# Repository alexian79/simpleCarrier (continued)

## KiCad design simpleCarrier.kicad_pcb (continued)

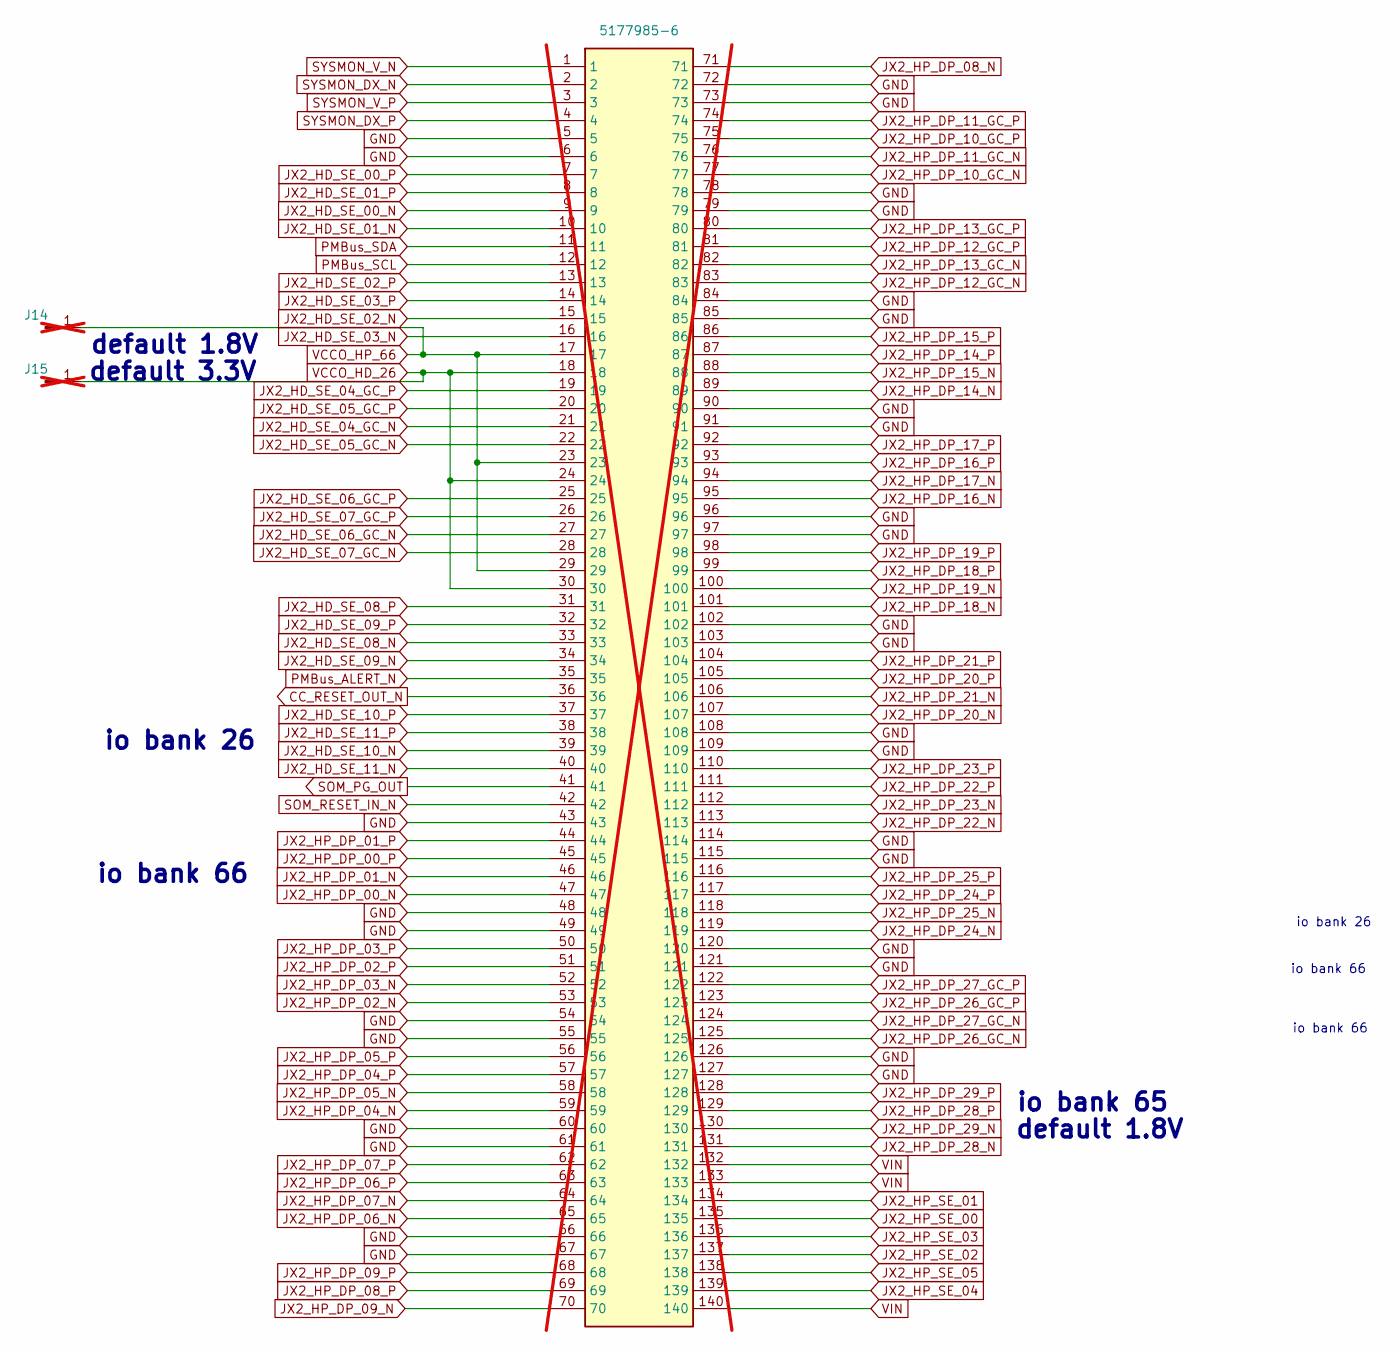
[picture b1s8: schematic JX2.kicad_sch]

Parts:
J14, J15: Conn_01x01_Pin; PinHeader_1x01_P2.00mm_Horizontal; not fitted
JX2: 5177985-6; Manufacturer_Part_Number 5177985-6; Mouser Part Number 571-5177985-6; not fitted

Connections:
CC_RESET_OUT_N: JX2.36
GND: JX2.5, JX2.6, JX2.43, JX2.48, JX2.49, JX2.54, JX2.55, JX2.60, JX2.61, JX2.66, JX2.67, JX2.72, JX2.73, JX2.78, JX2.79, JX2.84, JX2.85, JX2.90, JX2.91, JX2.96, JX2.97, JX2.102, JX2.103, JX2.108, JX2.109, JX2.114, JX2.115, JX2.120, JX2.121, JX2.126, JX2.127; also elsewhere on the board
JX2_HD_SE_00_N: JX2.9; also elsewhere on the board
JX2_HD_SE_00_P: JX2.7; also elsewhere on the board
JX2_HD_SE_01_N: JX2.10; also elsewhere on the board
JX2_HD_SE_01_P: JX2.8; also elsewhere on the board
JX2_HD_SE_02_N: JX2.15; also elsewhere on the board
JX2_HD_SE_02_P: JX2.13; also elsewhere on the board
JX2_HD_SE_03_N: JX2.16; also elsewhere on the board
JX2_HD_SE_03_P: JX2.14; also elsewhere on the board
JX2_HD_SE_04_GC_N: JX2.21
JX2_HD_SE_04_GC_P: JX2.19
JX2_HD_SE_05_GC_N: JX2.22; also elsewhere on the board
JX2_HD_SE_05_GC_P: JX2.20; also elsewhere on the board
JX2_HD_SE_06_GC_N: JX2.27; also elsewhere on the board
JX2_HD_SE_06_GC_P: JX2.25; also elsewhere on the board
JX2_HD_SE_07_GC_N: JX2.28; also elsewhere on the board
JX2_HD_SE_07_GC_P: JX2.26; also elsewhere on the board
JX2_HD_SE_08_N: JX2.33; also elsewhere on the board
JX2_HD_SE_08_P: JX2.31; also elsewhere on the board
JX2_HD_SE_09_N: JX2.34; also elsewhere on the board
JX2_HD_SE_09_P: JX2.32; also elsewhere on the board
JX2_HD_SE_10_N: JX2.39
JX2_HD_SE_10_P: JX2.37
JX2_HD_SE_11_N: JX2.40; also elsewhere on the board
JX2_HD_SE_11_P: JX2.38
JX2_HP_DP_00_N: JX2.47
JX2_HP_DP_00_P: JX2.45
JX2_HP_DP_01_N: JX2.46
JX2_HP_DP_01_P: JX2.44
JX2_HP_DP_02_N: JX2.53
JX2_HP_DP_02_P: JX2.51
JX2_HP_DP_03_N: JX2.52
JX2_HP_DP_03_P: JX2.50
JX2_HP_DP_04_N: JX2.59
JX2_HP_DP_04_P: JX2.57
JX2_HP_DP_05_N: JX2.58
JX2_HP_DP_05_P: JX2.56
JX2_HP_DP_06_N: JX2.65
JX2_HP_DP_06_P: JX2.63
JX2_HP_DP_07_N: JX2.64
JX2_HP_DP_07_P: JX2.62
JX2_HP_DP_08_N: JX2.71
JX2_HP_DP_08_P: JX2.69
JX2_HP_DP_09_N: JX2.70
JX2_HP_DP_09_P: JX2.68
JX2_HP_DP_10_GC_N: JX2.77
JX2_HP_DP_10_GC_P: JX2.75
JX2_HP_DP_11_GC_N: JX2.76
JX2_HP_DP_11_GC_P: JX2.74
JX2_HP_DP_12_GC_N: JX2.83; also elsewhere on the board
JX2_HP_DP_12_GC_P: JX2.81; also elsewhere on the board
JX2_HP_DP_13_GC_N: JX2.82
JX2_HP_DP_13_GC_P: JX2.80
JX2_HP_DP_14_N: JX2.89
JX2_HP_DP_14_P: JX2.87
JX2_HP_DP_15_N: JX2.88
JX2_HP_DP_15_P: JX2.86
JX2_HP_DP_16_N: JX2.95
JX2_HP_DP_16_P: JX2.93
JX2_HP_DP_17_N: JX2.94
JX2_HP_DP_17_P: JX2.92
JX2_HP_DP_18_N: JX2.101
JX2_HP_DP_18_P: JX2.99
JX2_HP_DP_19_N: JX2.100
JX2_HP_DP_19_P: JX2.98
JX2_HP_DP_20_N: JX2.107
JX2_HP_DP_20_P: JX2.105
JX2_HP_DP_21_N: JX2.106
JX2_HP_DP_21_P: JX2.104
JX2_HP_DP_22_N: JX2.113
JX2_HP_DP_22_P: JX2.111
JX2_HP_DP_23_N: JX2.112
JX2_HP_DP_23_P: JX2.110
JX2_HP_DP_24_N: JX2.119; also elsewhere on the board
JX2_HP_DP_24_P: JX2.117; also elsewhere on the board
JX2_HP_DP_25_N: JX2.118; also elsewhere on the board
JX2_HP_DP_25_P: JX2.116; also elsewhere on the board
JX2_HP_DP_26_GC_N: JX2.125; also elsewhere on the board
JX2_HP_DP_26_GC_P: JX2.123; also elsewhere on the board
JX2_HP_DP_27_GC_N: JX2.124; also elsewhere on the board
JX2_HP_DP_27_GC_P: JX2.122; also elsewhere on the board
JX2_HP_DP_28_N: JX2.131; also elsewhere on the board
JX2_HP_DP_28_P: JX2.129; also elsewhere on the board
JX2_HP_DP_29_N: JX2.130; also elsewhere on the board
JX2_HP_DP_29_P: JX2.128; also elsewhere on the board
JX2_HP_SE_00: JX2.135; also elsewhere on the board
JX2_HP_SE_01: JX2.134; also elsewhere on the board
JX2_HP_SE_02: JX2.137; also elsewhere on the board
JX2_HP_SE_03: JX2.136; also elsewhere on the board
JX2_HP_SE_04: JX2.139
JX2_HP_SE_05: JX2.138
PMBus_ALERT_N: JX2.35
PMBus_SCL: JX2.12
PMBus_SDA: JX2.11
SOM_PG_OUT: JX2.41; also elsewhere on the board
SOM_RESET_IN_N: JX2.42; also elsewhere on the board
SYSMON_DX_N: JX2.2
SYSMON_DX_P: JX2.4
SYSMON_V_N: JX2.1
SYSMON_V_P: JX2.3
VCCO_HD_26: J15.1, JX2.18, JX2.24, JX2.30; also elsewhere on the board
VCCO_HP_66: J14.1, JX2.17, JX2.23, JX2.29; also elsewhere on the board
VIN: JX2.132, JX2.133, JX2.140; also elsewhere on the board

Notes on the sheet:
default 1.8V
io bank 66
io bank 26
io bank 65
default 1.8V
default 3.3V

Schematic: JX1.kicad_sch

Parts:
J12, J13: Conn_01x01_Pin; PinHeader_1x01_P2.00mm_Horizontal; not fitted
JX1: 5177985-6; Manufacturer_Part_Number 5177985-6; Mouser Part Number 571-5177985-6; not fitted

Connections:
CLKOUT: JX1.64; also elsewhere on the board
DATA0: JX1.32; also elsewhere on the board
DATA1: JX1.34; also elsewhere on the board
DATA2: JX1.38; also elsewhere on the board
DATA3: JX1.40; also elsewhere on the board
DATA4: JX1.44; also elsewhere on the board
DATA5: JX1.46; also elsewhere on the board
DATA6: JX1.50; also elsewhere on the board
DATA7: JX1.52; also elsewhere on the board
DIR: JX1.28; also elsewhere on the board
GND: JX1.19, JX1.24, JX1.25, JX1.30, JX1.31, JX1.36, JX1.37, JX1.42, JX1.43, JX1.48, JX1.49, JX1.54, JX1.55, JX1.60, JX1.61, JX1.66, JX1.67, JX1.72, JX1.73, JX1.78, JX1.79, JX1.84, JX1.85, JX1.90, JX1.91, JX1.96, JX1.97, JX1.102, JX1.103, JX1.108, JX1.109, JX1.114, JX1.115, JX1.120, JX1.121, JX1.126, JX1.127; also elsewhere on the board
JTAG_TCK: JX1.1; also elsewhere on the board
JTAG_TDI: JX1.4; also elsewhere on the board
JTAG_TDO: JX1.3; also elsewhere on the board
JTAG_TMS: JX1.2; also elsewhere on the board
JX1_HP_DP_00_N: JX1.11
JX1_HP_DP_00_P: JX1.9
JX1_HP_DP_01_N: JX1.10
JX1_HP_DP_01_P: JX1.8
JX1_HP_DP_02_N: JX1.17
JX1_HP_DP_02_P: JX1.15
JX1_HP_DP_03_N: JX1.16
JX1_HP_DP_03_P: JX1.14
JX1_HP_DP_04_N: JX1.23
JX1_HP_DP_04_P: JX1.21
JX1_HP_DP_05_N: JX1.22; also elsewhere on the board
JX1_HP_DP_05_P: JX1.20
JX1_HP_DP_06_N: JX1.29; also elsewhere on the board
JX1_HP_DP_06_P: JX1.27
JX1_HP_DP_07_P: JX1.26; also elsewhere on the board
JX1_HP_DP_08_N: JX1.35
JX1_HP_DP_08_P: JX1.33
JX1_HP_DP_10_N: JX1.41
JX1_HP_DP_10_P: JX1.39
JX1_HP_DP_12_N: JX1.47
JX1_HP_DP_12_P: JX1.45; also elsewhere on the board
JX1_HP_DP_14_N: JX1.53
JX1_HP_DP_14_P: JX1.51
JX1_HP_DP_16_N: JX1.59; also elsewhere on the board
JX1_HP_DP_16_P: JX1.57; also elsewhere on the board
JX1_HP_DP_17_N: JX1.58
JX1_HP_DP_17_P: JX1.56
JX1_HP_DP_18_GC_N: JX1.65
JX1_HP_DP_18_GC_P: JX1.63; also elsewhere on the board
JX1_HP_DP_19_GC_P: JX1.62
JX1_HP_DP_20_GC_N: JX1.71; also elsewhere on the board
JX1_HP_DP_20_GC_P: JX1.69; also elsewhere on the board
JX1_HP_DP_21_GC_N: JX1.70
JX1_HP_DP_21_GC_P: JX1.68; also elsewhere on the board
JX1_HP_DP_22_N: JX1.77
JX1_HP_DP_22_P: JX1.75; also elsewhere on the board
JX1_HP_DP_23_N: JX1.76
JX1_HP_DP_23_P: JX1.74
JX1_HP_DP_24_N: JX1.83
JX1_HP_DP_24_P: JX1.81
JX1_HP_DP_25_N: JX1.82
JX1_HP_DP_25_P: JX1.80
JX1_HP_DP_26_N: JX1.89
JX1_HP_DP_26_P: JX1.87
JX1_HP_DP_27_N: JX1.88
JX1_HP_DP_27_P: JX1.86
JX1_HP_DP_28_N: JX1.95
JX1_HP_DP_28_P: JX1.93
JX1_HP_DP_29_N: JX1.94
JX1_HP_DP_29_P: JX1.92
JX1_HP_DP_30_N: JX1.101
JX1_HP_DP_30_P: JX1.99
JX1_HP_DP_31_N: JX1.100
JX1_HP_DP_31_P: JX1.98
JX1_HP_DP_32_N: JX1.107; also elsewhere on the board
JX1_HP_DP_32_P: JX1.105; also elsewhere on the board
JX1_HP_DP_33_N: JX1.106; also elsewhere on the board
JX1_HP_DP_33_P: JX1.104; also elsewhere on the board
JX1_HP_DP_34_N: JX1.113; also elsewhere on the board
JX1_HP_DP_34_P: JX1.111; also elsewhere on the board
JX1_HP_DP_35_N: JX1.112; also elsewhere on the board
JX1_HP_DP_35_P: JX1.110; also elsewhere on the board
JX1_HP_DP_36_GC_N: JX1.119; also elsewhere on the board
JX1_HP_DP_36_GC_P: JX1.117; also elsewhere on the board
JX1_HP_DP_37_GC_N: JX1.118; also elsewhere on the board
JX1_HP_DP_37_GC_P: JX1.116; also elsewhere on the board
JX1_HP_DP_38_N: JX1.125; also elsewhere on the board
JX1_HP_DP_38_P: JX1.123; also elsewhere on the board
JX1_HP_DP_39_N: JX1.124; also elsewhere on the board
JX1_HP_DP_39_P: JX1.122; also elsewhere on the board
JX1_HP_DP_40_N: JX1.131; also elsewhere on the board
JX1_HP_DP_40_P: JX1.129; also elsewhere on the board
JX1_HP_DP_41_N: JX1.130; also elsewhere on the board
JX1_HP_DP_41_P: JX1.128; also elsewhere on the board
JX1_HP_SE_00: JX1.135; also elsewhere on the board
JX1_HP_SE_01: JX1.134; also elsewhere on the board
JX1_HP_SE_02: JX1.137; also elsewhere on the board
JX1_HP_SE_03: JX1.136; also elsewhere on the board
JX1_HP_SE_04: JX1.139
JX1_HP_SE_05: JX1.138
VCCO_HP_64: J12.1, JX1.6, JX1.12, JX1.18; also elsewhere on the board
VCCO_HP_65: J13.1, JX1.5, JX1.7, JX1.13; also elsewhere on the board
VIN: JX1.132, JX1.133, JX1.140; also elsewhere on the board

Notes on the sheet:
+1.8V Default
+1.2V Default

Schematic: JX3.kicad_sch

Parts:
J16, J17, J18: Conn_01x01_Pin; PinHeader_1x01_P2.00mm_Horizontal; not fitted
JX3: 5177985-4; Manufacturer_Part_Number 5177985-4; Mouser Part Number 571-5177985-4; not fitted

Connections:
+1V8: J17.1, JX3.36, JX3.42; also elsewhere on the board
CC_INT_N: JX3.68
CC_SCL: JX3.44
CC_SDA: JX3.41
ETH_MD1_N: JX3.59; also elsewhere on the board
ETH_MD1_P: JX3.57; also elsewhere on the board
ETH_MD2_N: JX3.58; also elsewhere on the board
ETH_MD2_P: JX3.56; also elsewhere on the board
ETH_MD3_N: JX3.65; also elsewhere on the board
ETH_MD3_P: JX3.63; also elsewhere on the board
ETH_MD4_N: JX3.64; also elsewhere on the board
ETH_MD4_P: JX3.62; also elsewhere on the board
ETH_PHY_LED0: JX3.53; also elsewhere on the board
ETH_PHY_LED1: JX3.52; also elsewhere on the board
GND: JX3.2, JX3.5, JX3.8, JX3.11, JX3.14, JX3.16, JX3.17, JX3.19, JX3.22, JX3.24, JX3.25, JX3.30, JX3.43, JX3.49, JX3.54, JX3.55, JX3.60, JX3.61, JX3.66; also elsewhere on the board
GTR_REFCLK0_N: JX3.40; also elsewhere on the board
GTR_REFCLK0_P: JX3.38; also elsewhere on the board
GTR_REFCLK1_N: JX3.35
GTR_REFCLK1_P: JX3.33
GTR_REFCLK2_N: JX3.34
GTR_REFCLK2_P: JX3.32
GTR_REFCLK3_N: JX3.29
GTR_REFCLK3_P: JX3.27
GTR_RX0_N: JX3.28; also elsewhere on the board
GTR_RX0_P: JX3.26; also elsewhere on the board
GTR_RX1_N: JX3.20; also elsewhere on the board
GTR_RX1_P: JX3.18; also elsewhere on the board
GTR_RX2_N: JX3.12; also elsewhere on the board
GTR_RX2_P: JX3.10; also elsewhere on the board
GTR_RX3_N: JX3.6; also elsewhere on the board
GTR_RX3_P: JX3.4; also elsewhere on the board
GTR_TX0_N: JX3.23; also elsewhere on the board
GTR_TX0_P: JX3.21; also elsewhere on the board
GTR_TX1_N: JX3.15; also elsewhere on the board
GTR_TX1_P: JX3.13; also elsewhere on the board
GTR_TX2_N: JX3.9; also elsewhere on the board
GTR_TX2_P: JX3.7; also elsewhere on the board
GTR_TX3_N: JX3.3; also elsewhere on the board
GTR_TX3_P: JX3.1; also elsewhere on the board
I2C0_SCL: JX3.79, JX3.94; also elsewhere on the board
I2C0_SDA: JX3.80; also elsewhere on the board
MGTRAVCC: J16.1, JX3.31, JX3.37, JX3.39; also elsewhere on the board
MGTRAVCC_Sense: JX3.75
MGTRAVTT_Sense: JX3.76
MIO_26: JX3.69
MIO_27: JX3.70
MIO_28: JX3.71
MIO_29: JX3.72
MIO_30: JX3.73; also elsewhere on the board
MIO_31: JX3.74
MIO_32: JX3.77
MIO_33: JX3.78
MIO_36: JX3.81
MIO_37: JX3.82
MIO_38: JX3.85; also elsewhere on the board
MIO_39: JX3.86
MIO_40: JX3.87
MIO_41: JX3.88; also elsewhere on the board
MIO_42: JX3.89; also elsewhere on the board
MIO_43: JX3.90; also elsewhere on the board
MIO_44: JX3.93
MIO_46: JX3.95; also elsewhere on the board
MIO_47: JX3.96; also elsewhere on the board
MIO_48: JX3.97
MIO_49: JX3.98
MIO_50: JX3.99
MIO_51: JX3.100
PS_VBATT: JX3.46
USB_ID: JX3.51; also elsewhere on the board
USB_OTG_CPEN: JX3.48; also elsewhere on the board
USB_OTG_N: JX3.47; also elsewhere on the board
USB_OTG_P: JX3.45; also elsewhere on the board
USB_OTG_VBUS: JX3.50; also elsewhere on the board
VCCO_HD_26_Sense: JX3.84
VCCO_HP_64_Sense: JX3.92
VCCO_HP_65_Sense: JX3.91
VCCO_HP_66_Sense: JX3.83
VCCO_PSIO_501: J18.1, JX3.67; also elsewhere on the board

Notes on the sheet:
default 3.3V

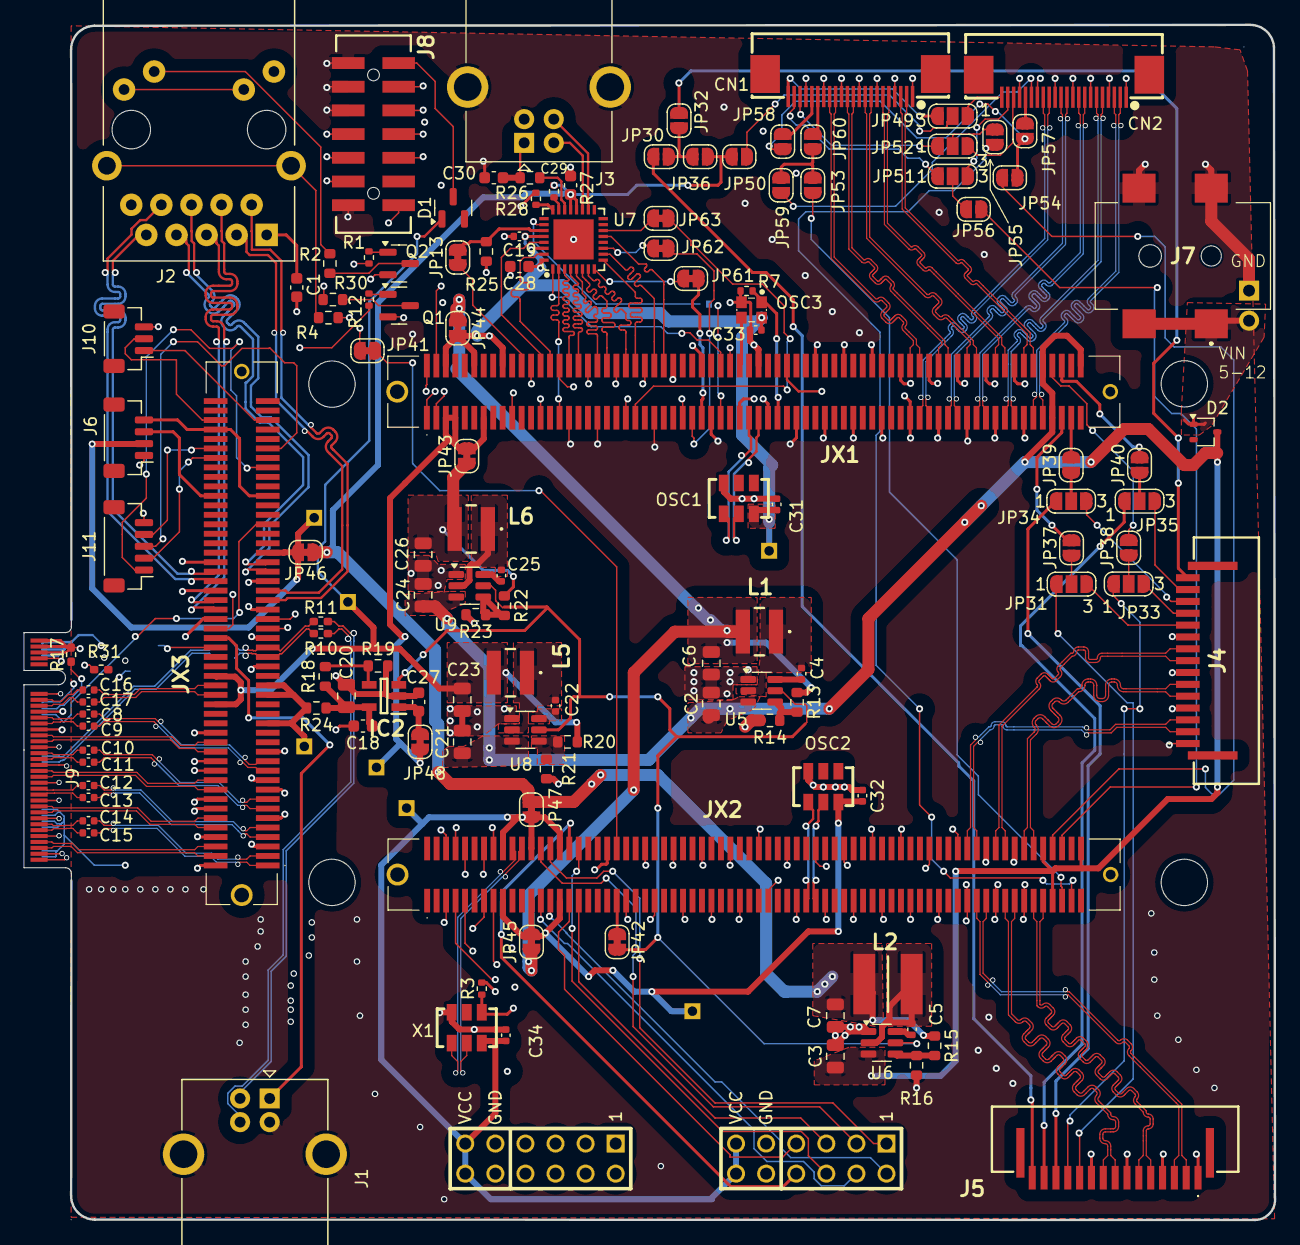
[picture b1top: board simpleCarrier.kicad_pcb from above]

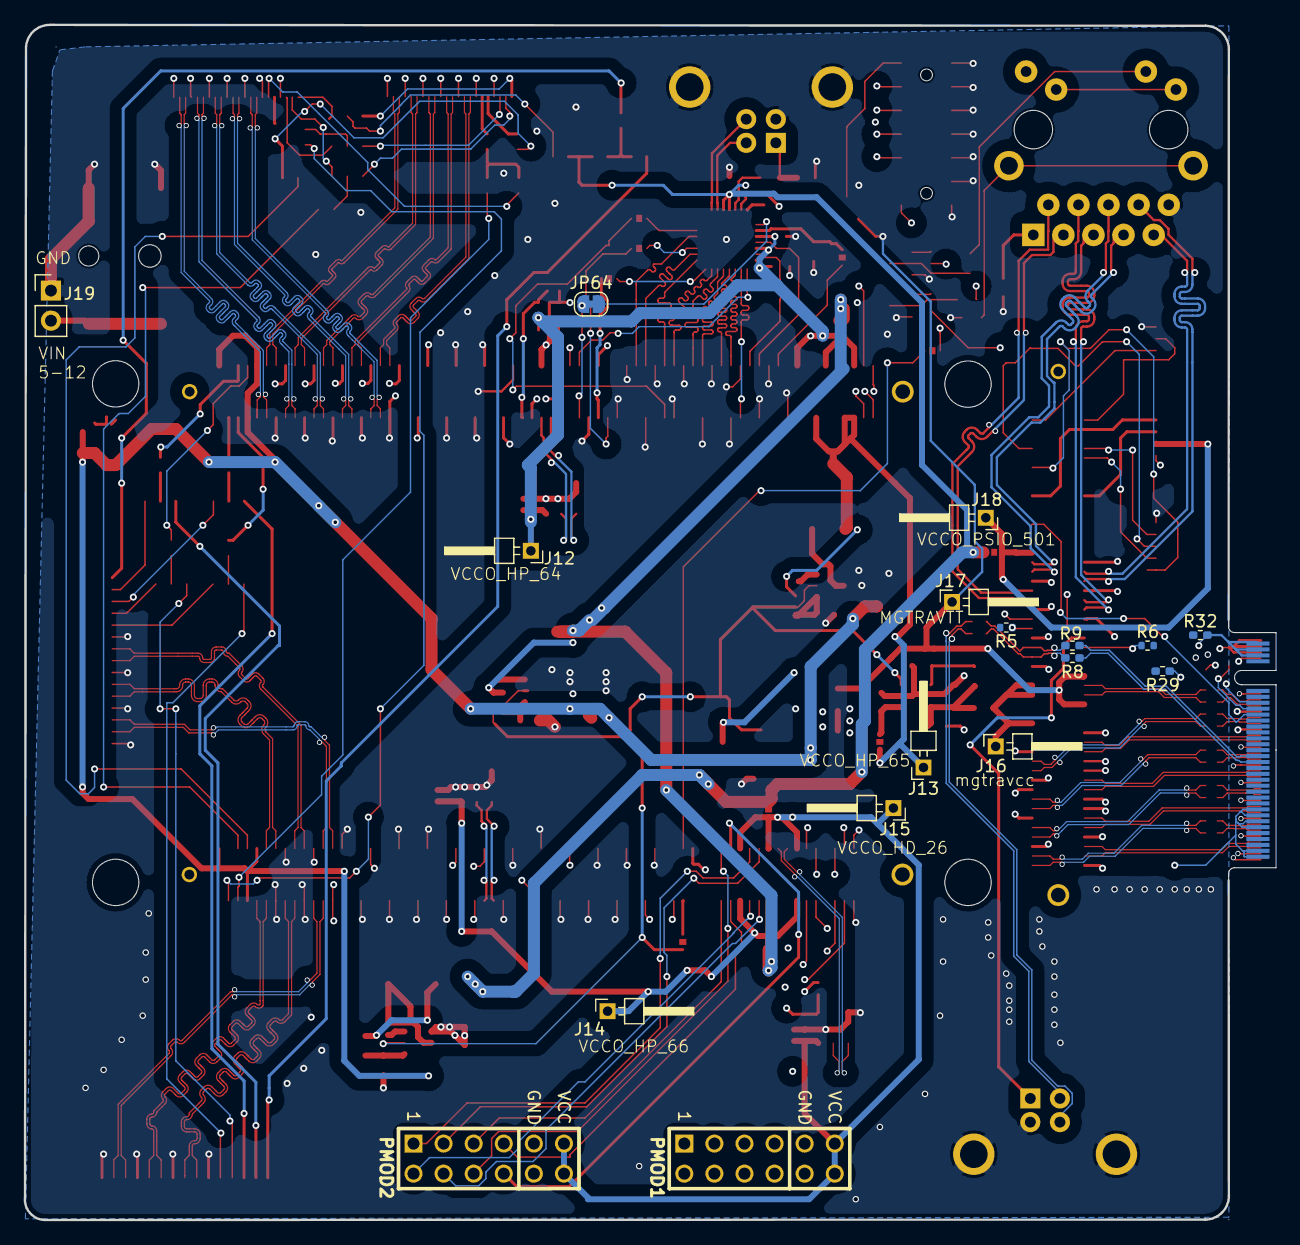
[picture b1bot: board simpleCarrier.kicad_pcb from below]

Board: 6 copper layers, 105.5 x 100.9 mm, 146 parts (17 on the bottom side), 228 nets.

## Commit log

2024-10-06 initial, layout finished but has a lot of DRC errors
2024-10-11 removed all resistors 0201mm, changed to 0402mm
2024-10-12 moved to 6 layers, fixing DRC issues
2024-10-13 moved jtag connector, added holes for all power supplies, fixed most of DRC
2024-10-18 marked more connectors as do not solder.
2024-10-30 fixed unconnected test point for VCC 501
2024-10-30 fixed jtag vref was not connected to 1.8V
